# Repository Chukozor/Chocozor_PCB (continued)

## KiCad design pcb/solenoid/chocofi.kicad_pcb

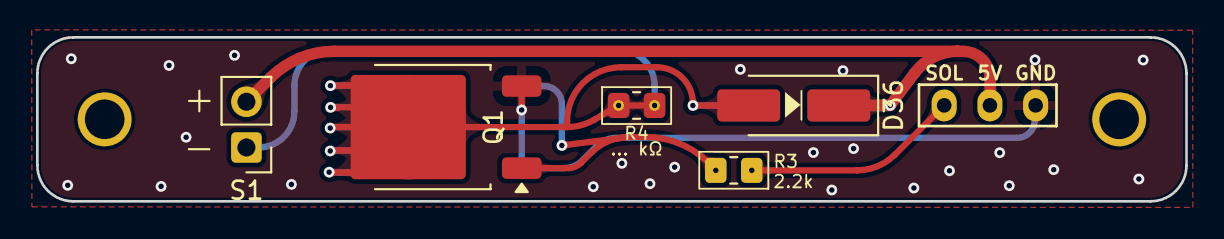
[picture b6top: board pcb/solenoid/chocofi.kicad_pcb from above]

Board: 2 copper layers, 63.8 x 9.1 mm, 8 parts (0 on the bottom side), 5 nets.

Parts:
D36: SS14 (or M1) package SMA; D_SMA_Handsoldering-Chuk
J3: Conn_01x03; solenoid_ribon_connector
M2-2, M2-3: MountingHoleM2; Mounting-hole-M2
Q1: TIP120; TO-252-2-reversible
R3: 2.2k; R_0805_double_face_Chukozor
R4: ... kΩ; R_0805_double_face_Chukozor-Optional
S1: Solenoid-PinHeader_1x02_P2.54mm_Vertical-Chuk

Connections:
GND_Solenoid_side: J3.1, Q1.3 (E)
unnamed: D36.2 (A), Q1.2 (C), R4.1, R4.2, S1.1 (GND)
unnamed: Q1.1 (B), R3.2
SolenoidPin_Solenoid_side: J3.3, R3.1
VBUS_Solenoid_side: D36.1 (K), J3.2, S1.2 (5V)

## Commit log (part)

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2025-07-31 prble de ground plane
2025-08-02 begining of clean thumb routage
2025-08-06 wip add vias for GND
2025-08-07 silkscreen overlaping warning
2025-08-08 last commit before generating gerbers
2025-08-09 Gerbers MainBody V2
2025-08-09 Whole BOM and CPL
2025-08-09 add gerber of Flick V1
2025-08-09 gerbers Flick 2
2025-08-09 modifications for stencil
2025-08-10 added Flick 4
2025-08-10 replacement some FPC TH near FPC by vias
2025-08-10 again vias for FPC connectors
2025-08-10 same
2025-08-10 no more issue with VIA
2025-08-11 Flick 1 and 4 panel and gerbers added
2025-08-11 adding some gerbers
2025-08-11 gerbers of Chocozor V2
2025-08-16 wip : schematics and PCB
2025-08-16 replacement FPC thumbs by solder pins
2025-08-16 good for exporting gerbers
2025-08-17 gerbers for V2.8/V2.7
2025-08-17 Add Lateral Thumb PCB (for keycaps)
2025-08-17 Add gerbers of Mobile Thumbs
2025-08-25 symetric hand for matrix coordinates
2025-08-29 added some .STEP files for the case
2025-08-29 again, added some .STEP files for the case
2025-08-29 follow up on the PCB footprint update
2025-08-31 wip : add some .STEP files for case
2025-08-31 wip again, added some .STEP files for the case
2025-08-31 wip : modifications of steps and add step files
2025-08-31 adjustments after merge
2025-09-01 wip steps and zoffset -0.085mm
2025-09-01 wip step
2025-09-07 add STEP file for one switch top plate, and modify reset button STEP file.
2025-09-07 comment non used (yet) command lines of script.
2025-09-07 modification of some STEP files and some footprint
2025-09-13 modification numbers of rows for convenience (to make the JSON in QMK)
2025-09-14 add pro-micro pinout
2025-09-14 add breadboard pcb
2025-09-14 add breadboard gerbers
2025-09-19 wip Case
2025-12-25 steps files for top case with original copy of PG1350 saved in "PC1350-socket-OrigiNAL.step"
2025-12-29 Add datasheet of Alpines rotary encoder EC12
2025-12-31 position for RGB matrix in the .json
2026-01-07 Added Procyon schematics with Chocozor schematics side by side
2026-01-10 ajout emplacement big oled
2026-01-11 add original switch plate
2026-01-11 beginning of new mobil switch
2026-01-11 continuation du petit mobil switch
2026-01-11 The three mini PCB are finished and ready for exportation (mini switch connecteur, microswitch connecteur, EC12 connector (Michal)
2026-01-11 run DRC et corrections
2026-01-12 Fix some DRC issues and modify the pcb for the Solenoid : it's now another shape
2026-01-13 add new footprint for the mosfet of solenoid
2026-01-15 modification de l'encodeur, et ajout du la connection d'un switch de bout de pouce en Mobil Switch
2026-01-16 WIP et réorganisation des fichiers dans le dossier "docs-some_components"
2026-01-17 wip (encoder mieux)
2026-01-17 adding some components caracteristics
2026-01-18 Ajout du Procyon ("footprint"+ symbol)
2026-01-18 WIP procyon
2026-01-18 add dimensions of big oled
2026-01-18 add Azoteq TPS65 in userdrawings
2026-01-23 some DRC corrections
2026-01-23 paste layers wip
2026-01-23 idem
2026-01-24 add FPC connectors for stencil
2026-01-25 wip (drawing of azoteq TPS65)
2026-01-25 TRRS modification
2026-01-25 gerbers order JLC
2026-01-26 fix TRRS 3d model
2026-01-26 add picture of 2.9's PCB
2026-01-28 Removing the small holes of the keyswitches.
2026-01-28 updating footprints on PCB (no more useless little holes on PCB)
2026-01-29 better VCC line and other small stuffs
2026-02-08 add another mobil switch (MobilSW6) : smaller than the regular one.
2026-02-08 filet some tracks
2026-02-10 bidouille EC12
2026-02-11 edit wrong drawing
2026-02-17 correction of the EC12 mounting holes
2026-02-18 close edge of ec12
2026-02-18 better LED
2026-02-19 modification some STEP files for the case, and add of PCB design progress
2026-02-19 PCB skill tree
2026-03-03 modif piste de sorte à ce que SCK ait un plan de masse continue dessous
2026-03-09 commencé à mettre le branchement de l'encodeur de l'autre coté (mais pas encore fini).
2026-03-09 vias du plan de masse un peu mieux
2026-03-14 add a hole and improve a bit tracks for encoder
2026-03-19 improvement of PCB (mainly the rotary encoder connexion)
